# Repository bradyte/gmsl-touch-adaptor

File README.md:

Simple adaptor boards for passing touchscreen communication through GMSL EV Kits.

Used with:
* [MAX96751EVKIT](https://www.analog.com/en/products/max96751.html)
* [MAX96752EVKIT](https://www.analog.com/en/products/max96752.html)

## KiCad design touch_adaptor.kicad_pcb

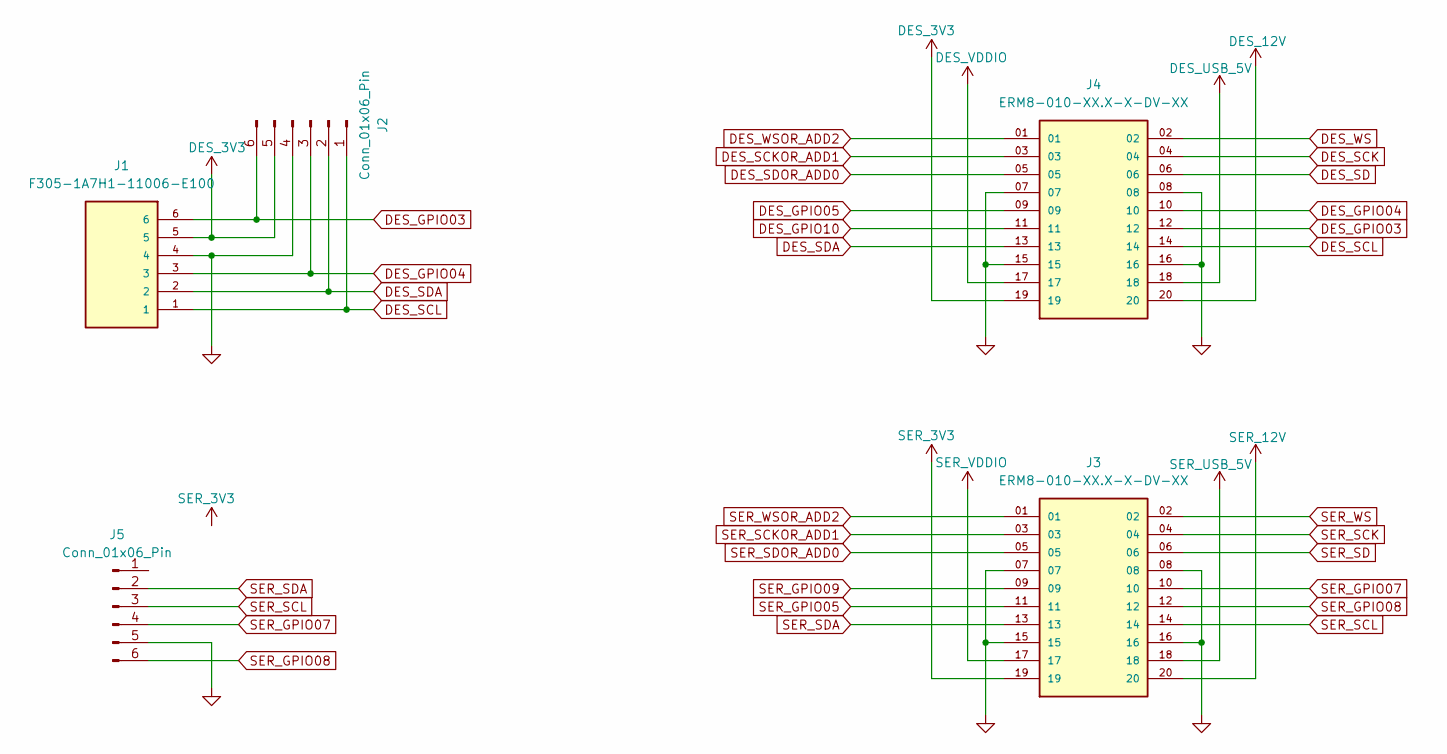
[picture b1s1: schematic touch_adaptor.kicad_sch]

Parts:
J1: F305-1A7H1-11006-E100; AMPHENOL_F305-1A7H1-11006-E100; PARTREV B
J2, J5: Conn_01x06_Pin; PinSocket_1x06_P2.54mm_Vertical
J3, J4: ERM8-010-XX.X-X-DV-XX; SAMTEC_ERM8-010-XX.X-X-DV-XX; PARTREV L

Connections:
DES_3V3: J1.5, J2.5, J4.19
DES_12V: J4.20
DES_GPIO05: J4.11
DES_GPIO07: J1.3, J2.3, J4.10
DES_GPIO08: J1.6, J2.6, J4.12
DES_GPIO09: J4.09
DES_SCK: J4.04
DES_SCKOR_ADD1: J4.03
DES_SCL: J1.1, J2.1, J4.14
DES_SD: J4.06
DES_SDA: J1.2, J2.2, J4.13
DES_SDOR_ADD0: J4.05
DES_USB_5V: J4.18
DES_VDDIO: J4.17
DES_WS: J4.02
DES_WSOR_ADD2: J4.01
GND: J1.4, J2.4, J3.07, J3.08, J3.15, J3.16, J4.07, J4.08, J4.15, J4.16, J5.5
SER_3V3: J3.19
SER_12V: J3.20
SER_GPIO05: J3.11
SER_GPIO07: J3.10, J5.4
SER_GPIO08: J3.12, J5.6
SER_GPIO09: J3.09
SER_SCK: J3.04
SER_SCKOR_ADD1: J3.03
SER_SCL: J3.14, J5.3
SER_SD: J3.06
SER_SDA: J3.13, J5.2
SER_SDOR_ADD0: J3.05
SER_USB_5V: J3.18
SER_VDDIO: J3.17
SER_WS: J3.02
SER_WSOR_ADD2: J3.01

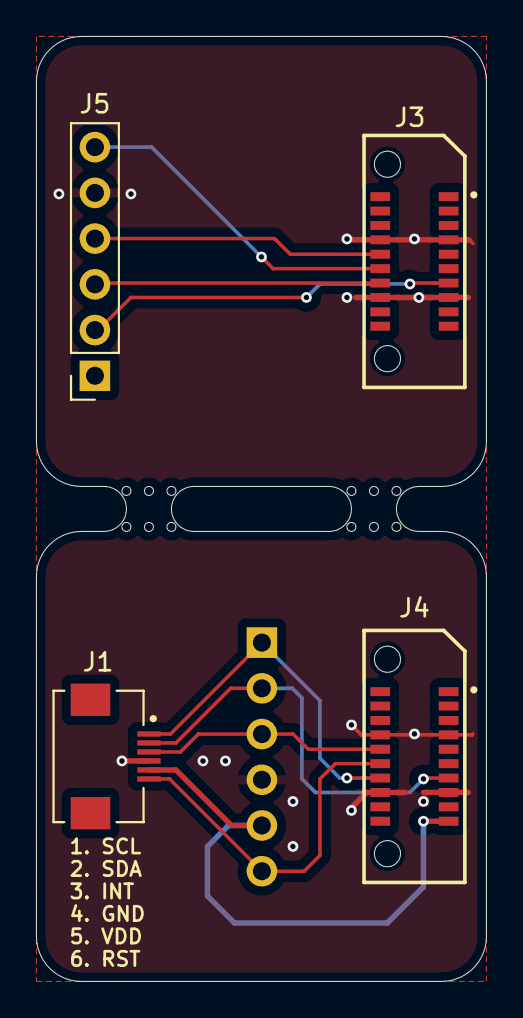
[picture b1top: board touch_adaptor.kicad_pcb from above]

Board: 2 copper layers, 25.0 x 52.5 mm, 5 parts (1 on the bottom side), 10 nets.

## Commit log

2024-10-02 initial upload
2024-10-02 cleaned up folders
